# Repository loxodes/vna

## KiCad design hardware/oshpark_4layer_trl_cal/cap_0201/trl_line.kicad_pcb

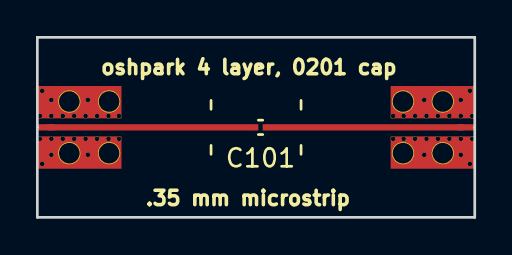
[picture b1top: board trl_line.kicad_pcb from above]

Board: 4 copper layers, 24.3 x 10.0 mm, 3 parts (0 on the bottom side), 3 nets.

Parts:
C101: C_Small; C_0201
U101, U102: CONN_SMA_2GND; SMA_901-10512_6p7MIL_FR408_CPW_LAUNCH

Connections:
GND: U101.2, U101.3, U102.2, U102.3
unnamed: C101.1, U102.1
unnamed: C101.2, U101.1

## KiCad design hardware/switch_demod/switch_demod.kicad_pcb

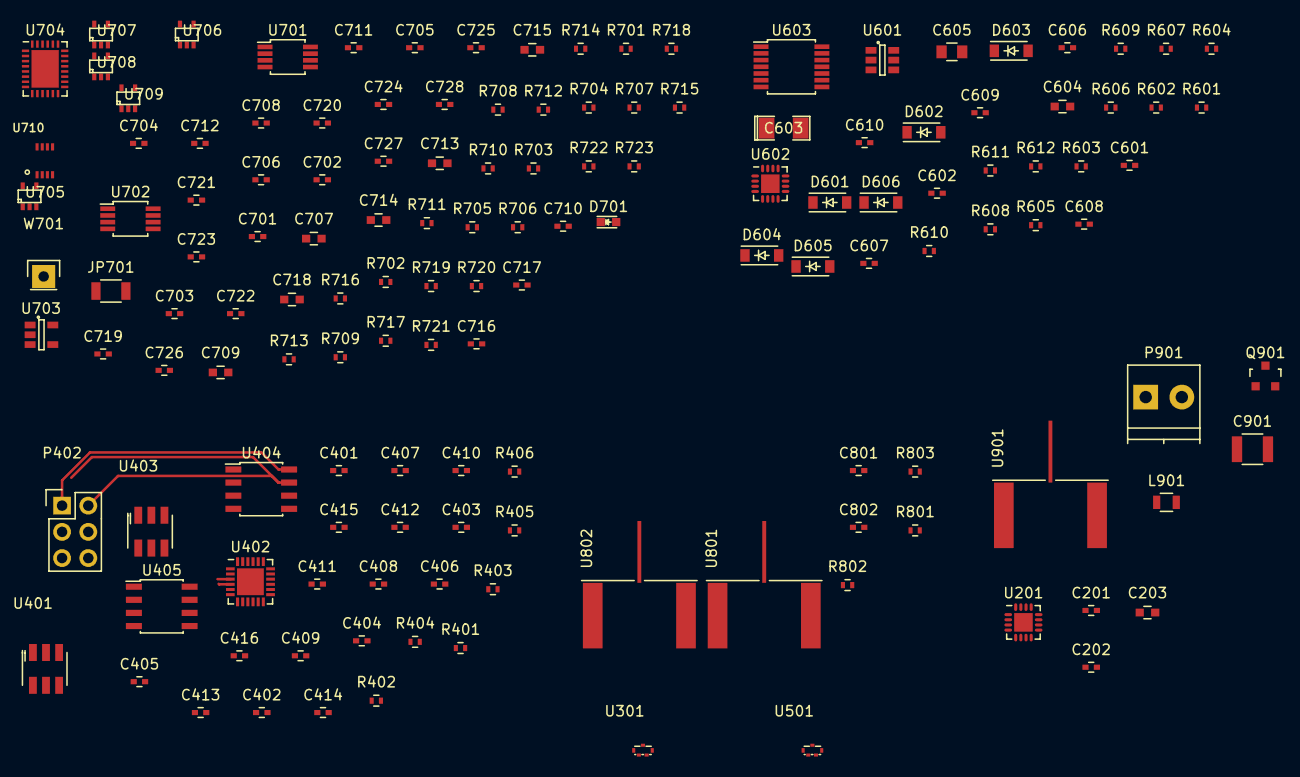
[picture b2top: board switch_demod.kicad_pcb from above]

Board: 4 copper layers, 141 parts (0 on the bottom side), 98 nets.

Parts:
C201, C202, C401, C404, C405, C406, C407, C408, C409, C410, C412, C606, C609: 100 pF; C_0402
C203, C604, C707, C709, C713, C714, C718: 10 uF; C_0603
C402, C403, C411, C413, C414, C415, C416, C602, C607, C701, C702, C705, C706, C708, C711, C712, C719, C720, C721, C722, C723, C724, C725, C726, C727, C728: 100 nF; C_0402
C601, C608: 30 pF; C_0402
C603: 10 uF TANT; SMD-1206_Pol
C605: C_Small; C_0805
C610, C801, C802: C_Small; C_0402
C703, C704: 220 pF; C_0402
C710, C716, C717: 1 uF; C_0402
C715: 10 nF; C_0603
C901: 100 uF; C_1210
D601, D602, D603, D604, D605, D606: 3.3V; SOD-123
D701: LED; LED_0603
JP701: JUMPER; R_1206
L901: FERRITE CHIP; R_0805
P402: CONN_02X03; Pin_Header_Straight_2x03
P901: CONN_01X02; TerminalBlock_Pheonix_PT-3.5mm_2pol
Q901: DMG2305UX; SOT-23
R401, R403, R404, R405, R406, R601, R602, R603, R610, R611, R612: 10k; R_0402
R402: 470; R_0402
R604, R605, R606, R607, R608, R609: 100; R_0402
R701, R702, R704, R706, R716: 0; R_0402
R703, R717, R718, R801, R802, R803: 1k; R_0402
R705, R707, R713: DNP; R_0402
R708, R709, R710, R711, R714, R715: 25; R_0402
R712, R719, R720, R721, R722, R723: 10; R_0402
U201: PE42521; QFN-16-1EP_3x3mm_Pitch0.5mm
U301, U501: PWR_SPLITTER; PS1608
U401, U403: TCM-63AX+; TCM1-63AX+
U402: ADL5380; QFN-24-1EP_4x4mm_Pitch0.5mm
U404, U405: LTC1566-1; SOIC-8_3.9x4.9mm_Pitch1.27mm
U601: LTC1983; SOT-23-6
U602: HMC424; QFN-16-1EP_3x3mm_Pitch0.5mm
U603: 74HC04_FULL; TSSOP-14_4.4x5mm_Pitch0.65mm
U701, U702: LT1819; MSOP-8_3x3mm_Pitch0.65mm
U703: TPS793; SOT-23-5
U704: LTC2323; QFN-28-1EP_4x5mm_Pitch0.5mm
U705, U706, U707, U708, U709: NC7SVU04; SC-70-5
U710: NC7SV74KBX; US8
U801, U802, U901: CONN_SMA_2GND; 142-0721-882_sma_cutout
W701: TEST_1P; Pin_Header_Straight_1x01

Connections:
+2V5: C718.1, C719.1, C720.1, C722.2, C728.2, D701.2, JP701.2, R716.2, R723.1, U703.5, U704.14, U706.5, U710.7, U710.8
+5V: C202.1, C203.1, C402.2, C403.2, C404.2, C405.2, C410.2, C411.2, C415.2, C416.2, C601.2, C602.2, C603.1, C701.2, C702.2, C705.1, C706.1, C707.1, C708.1, C709.1, C710.2, C727.1, C901.1, L901.1, R402.1, R405.1, R406.1, U201.16, U402.6, U402.13, U402.24, U404.6, U405.6, U601.1, U601.6, U701.8, U702.8, U703.1, U703.3, U704.1, U704.8, U704.28
/adc/ADC_CLKOUT: R719.2, U704.17, U705.4
/adc/ADC_CONV_CLK_IN: C721.2, R714.2
/adc/ADC_CONV_CLK_OUT: U707.4, U710.1
/adc/ADC_I_N: P402.6, R707.2, U405.7, U702.5
/adc/ADC_I_P: P402.5, U405.8, U702.3
/adc/ADC_Q_N: P402.2, R705.2, U404.7, U701.5
/adc/ADC_Q_P: P402.1, U404.8, U701.3
/adc/ADC_SCK: R722.2, U704.21, U706.4
/adc/ADC_SDO1: R720.2, U704.15, U708.4
/adc/ADC_SDO2: R721.2, U704.19, U709.4
/adc/ADC_~CONV: U704.9, U710.3
/adc/AIN1+: C704.1, R710.1, U704.7
/adc/AIN1-: C704.2, R711.1, U704.6
/adc/AIN2+: C703.1, R708.1, U704.2
/adc/AIN2-: C703.2, R709.1, U704.3
/attenuator/ATT_IN: C606.2, U501.3
/attenuator/ATT_OUT: C609.1, U301.3
/attenuator/V1: R604.2, U602.9
/attenuator/V2: R605.2, U602.8
/attenuator/V3: R606.2, U602.7
/attenuator/V4: R609.1, U602.6
/attenuator/V5: R608.1, U602.5
/attenuator/V6: R607.1, U602.4
/connectors_control_pow/DEMOD_ENBL: R401.1, U402.7
/demod/DEMOD_LO: C412.2, U501.2
/demod/DEMOD_RF: C401.2, U201.7
/demod/I_ADL_N: U402.4, U405.2
/demod/I_ADL_P: U402.3, U405.1
/demod/LO_I_N: C408.1, U402.10
/demod/LO_I_P: C409.1, U402.9
/demod/LO_Q_N: C407.1, U402.21
/demod/LO_Q_P: C406.1, U402.22
/demod/Q_ADL_N: U402.15, U404.2
/demod/Q_ADL_P: U402.16, U404.1
/panel connectors/DUT_PORT1: C801.2, U301.1
/panel connectors/DUT_PORT2: C802.2, U201.11
/splitter_input/RF2: C201.1, U301.2
/splitter_lo/RFC: U501.1, U901.1
GND: C202.2, C203.2, C402.1, C403.1, C404.1, C405.1, C410.1, C411.1, C413.2, C414.2, C415.1, C416.1, C601.1, C602.1, C603.2, C604.2, C607.1, C608.1, C610.1, C701.1, C702.1, C705.2, C706.2, C707.2, C708.2, C709.2, C710.1, C715.2, C716.2, C717.2, C718.2, C719.2, C720.2, C722.1, C723.1, C724.1, C725.1, C726.1, C727.2, C728.1, C901.2, P402.3, P402.4, P901.2, Q901.1, R401.2, R403.2, R404.2, R703.1, R705.1, R707.1, R712.1, R713.2, R715.1, R718.1, R801.1, R802.1, R803.1, U201.1, U201.3, U201.4, U201.5, U201.6, U201.8, U201.9, U201.10, U201.12, U201.13, U201.15, U201.17, U301.4, U401.3, U402.1, U402.2, U402.5, U402.8, U402.11, U402.14, U402.17, U402.18, U402.20, U402.23, U402.25, U403.3, U404.4, U405.4, U501.4, U601.5, U602.1, U602.3, U602.10, U602.12, U602.17, U603.14, U701.4, U702.4, U703.2, U704.4, U704.5, U704.10, U704.23, U704.29, U705.3, U706.3, U707.3, U708.3, U709.3, U710.4, U801.2, U801.3, U802.2, U802.3, U901.2, U901.3, W701.1
unnamed: C201.2, U201.2
unnamed: C401.1, U401.2
unnamed: C406.2, U401.6
unnamed: C407.2, U401.4
unnamed: C408.2, U403.6
unnamed: C409.2, U403.4
unnamed: C412.1, U403.2
unnamed: C413.1, R403.1, R405.2, U404.3, U404.5
unnamed: C414.1, R404.1, R406.2, U405.3, U405.5
unnamed: C605.1, U601.4
unnamed: C605.2, U601.3
unnamed: C606.1, U602.2
unnamed: C609.2, U602.11
unnamed: C711.1, C713.1, U704.26
unnamed: C711.2, C713.2, U704.27
unnamed: C712.1, C714.1, U704.12
unnamed: C712.2, C714.2, U704.11
unnamed: C715.1, U703.4
unnamed: C716.1, U704.24
unnamed: C717.1, U704.13
unnamed: C721.1, R717.1, R718.2, U707.2
unnamed: C724.2, R716.1, R717.2, U707.5
unnamed: C801.1, U801.1
unnamed: C802.1, U802.1
unnamed: D601.2, R601.1, U603.1
unnamed: D602.2, R602.1, U603.3
unnamed: D603.2, R603.1, U603.5
unnamed: D604.2, R612.1, U603.13
unnamed: D605.2, R611.1, U603.11
unnamed: D606.2, R610.1, U603.9
unnamed: D701.1, R703.2
unnamed: L901.2, Q901.2
unnamed: R402.2, U402.19
unnamed: R604.1, U603.2
unnamed: R605.1, U603.4
unnamed: R606.1, U603.6
unnamed: R607.2, U603.12
unnamed: R608.2, U603.10
unnamed: R609.2, U603.8
unnamed: R701.1, U701.2
unnamed: R701.2, R708.2, U701.1
unnamed: R702.1, U702.2
unnamed: R702.2, R710.2, U702.1
unnamed: R704.1, R709.2, U701.7
unnamed: R704.2, U701.6
unnamed: R706.1, R711.2, U702.7
unnamed: R706.2, U702.6
unnamed: R712.2, U704.25
unnamed: R713.1, U704.18
unnamed: R714.1, R715.2
unnamed: R719.1, U705.2
unnamed: R720.1, U708.2
unnamed: R721.1, U709.2
unnamed: R722.1, U706.2
unnamed: R723.2, U710.2
VEE: C604.1, C607.2, C608.2, C610.2, R601.2, R602.2, R603.2, R610.2, R611.2, R612.2, U601.2, U602.15, U603.7
VMEM: C723.2, C725.2, C726.2, JP701.1, U705.5, U708.5, U709.5

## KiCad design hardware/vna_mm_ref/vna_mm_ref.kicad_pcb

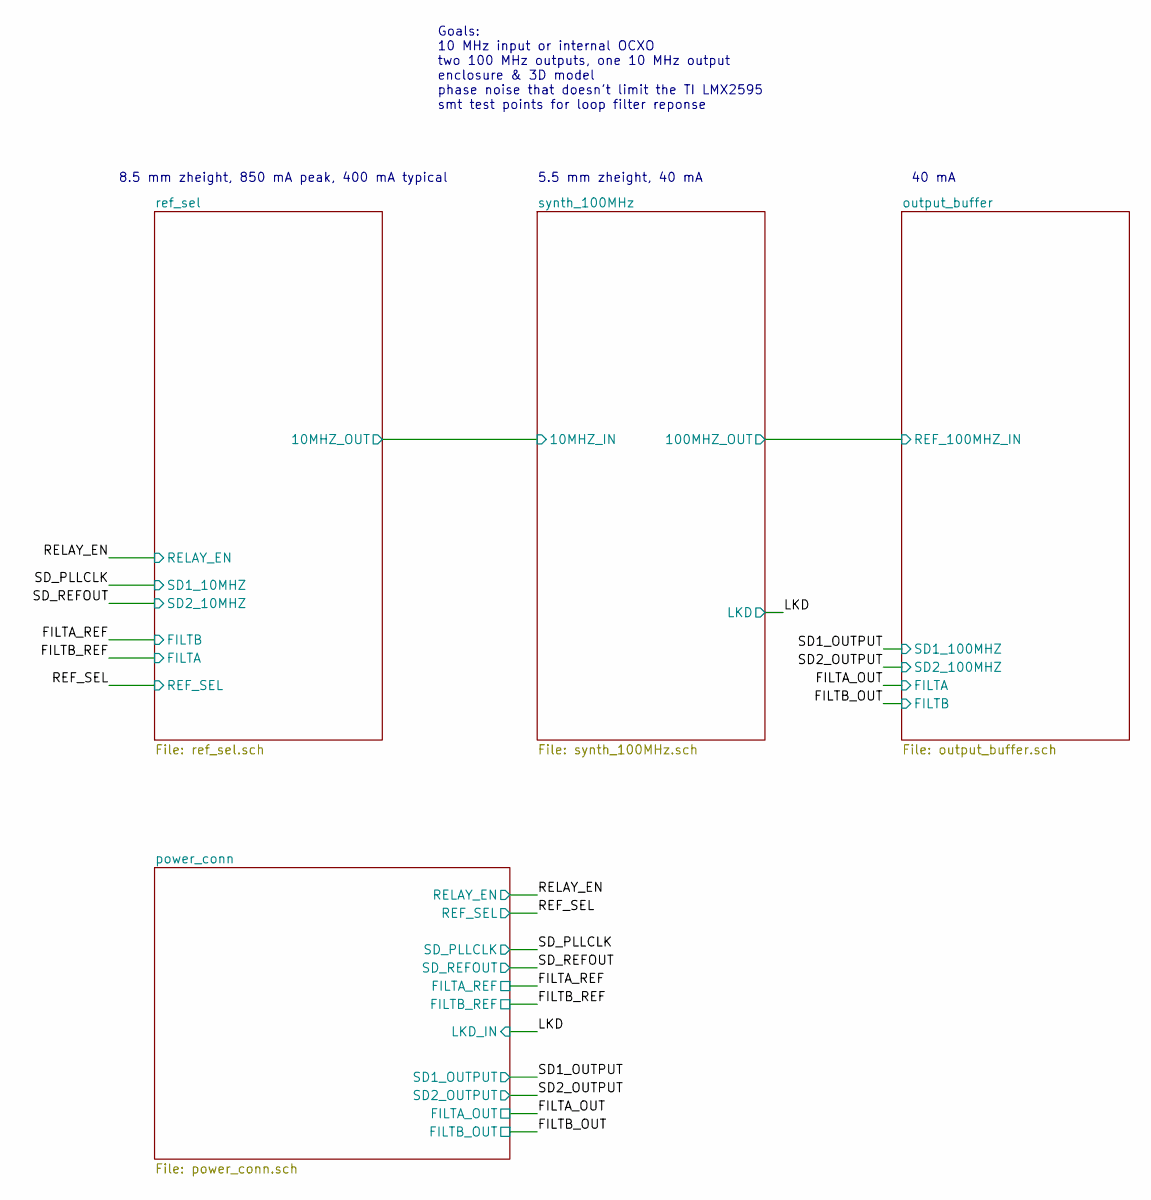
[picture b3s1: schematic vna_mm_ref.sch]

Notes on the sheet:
Goals: 10 MHz input or internal OCXO two 100 MHz outputs, one 10 MHz output enclosure & 3D model phase noise that doesn't limit the TI LMX2595 smt test points for loop filter reponse
8.5 mm zheight, 850 mA peak, 400 mA typical
5.5 mm zheight, 40 mA
40 mA

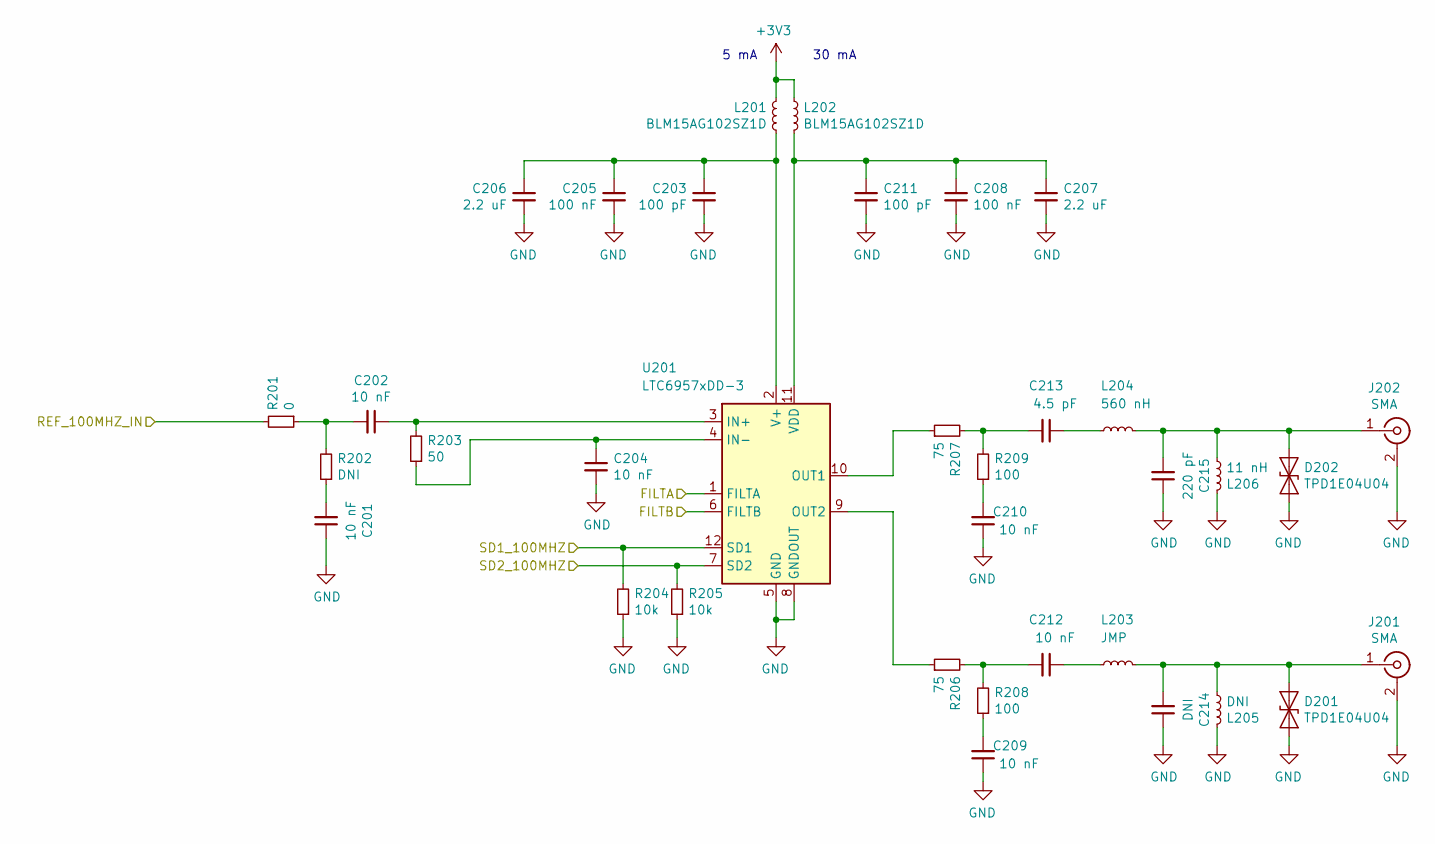
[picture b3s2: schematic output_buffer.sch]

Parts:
C201, C202, C204, C209, C210, C212: 10 nF; C_0402_1005Metric
C203, C211: 100 pF; C_0402_1005Metric
C205, C208: 100 nF; C_0402_1005Metric
C206, C207: 2.2 uF; C_0603_1608Metric
C213: 4.5 pF; C_0402_1005Metric
C214: DNI; C_0402_1005Metric
C215: 220 pF; C_0402_1005Metric
D201, D202: TPD1E04U04; D_0402_1005Metric
J201, J202: SMA; SMA_Amphenol_132289_EdgeMount
L201, L202: BLM15AG102SZ1D; L_0402_1005Metric
L203: JMP; L_0805_2012Metric
L204: 560 nH; L_0805_2012Metric
L205: DNI; L_0402_1005Metric
L206: 11 nH; L_0402_1005Metric
R201: 0; R_0402_1005Metric
R202: DNI; R_0402_1005Metric
R203: 50; R_0402_1005Metric
R204, R205: 10k; R_0402_1005Metric
R206, R207: 75; R_0402_1005Metric
R208, R209: 100; R_0402_1005Metric
U201: LTC6957xDD-3; DFN-12-1EP_3x3mm_P0.45mm_EP1.66x2.38mm

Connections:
+3V3: L201.1, L202.1; also elsewhere on the board
/FILTA_OUT: U201.1 (FILTA); also elsewhere on the board
/FILTB_OUT: U201.6 (FILTB); also elsewhere on the board
/SD1_OUTPUT: R204.2, U201.12 (SD1); also elsewhere on the board
/SD2_OUTPUT: R205.2, U201.7 (SD2); also elsewhere on the board
/synth_100MHz/100MHZ_OUT: R201.2; also elsewhere on the board
GND: C201.1, C203.2, C204.2, C205.2, C206.2, C207.2, C208.2, C209.1, C210.1, C211.2, C214.1, C215.1, D201.2 (A2), D202.2 (A2), J201.2 (Ext), J202.2 (Ext), L205.1, L206.1, R204.1, R205.1, U201.5 (GND), U201.8 (GNDOUT), U201.13 (GND); also elsewhere on the board
unnamed: C201.2, R202.1
unnamed: C202.1, R203.2, U201.3 (IN+)
unnamed: C202.2, R201.1, R202.2
unnamed: C203.1, C205.1, C206.1, L201.2, U201.2 (V+)
unnamed: C204.1, R203.1, U201.4 (IN-)
unnamed: C207.1, C208.1, C211.1, L202.2, U201.11 (VDD)
unnamed: C209.2, R208.1
unnamed: C210.2, R209.1
unnamed: C212.1, L203.2
unnamed: C212.2, R206.2, R208.2
unnamed: C213.1, L204.2
unnamed: C213.2, R207.2, R209.2
unnamed: C214.2, D201.1 (A1), J201.1 (In), L203.1, L205.2
unnamed: C215.2, D202.1 (A1), J202.1 (In), L204.1, L206.2
unnamed: R206.1, U201.9 (OUT2)
unnamed: R207.1, U201.10 (OUT1)

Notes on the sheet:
5 mA
30 mA

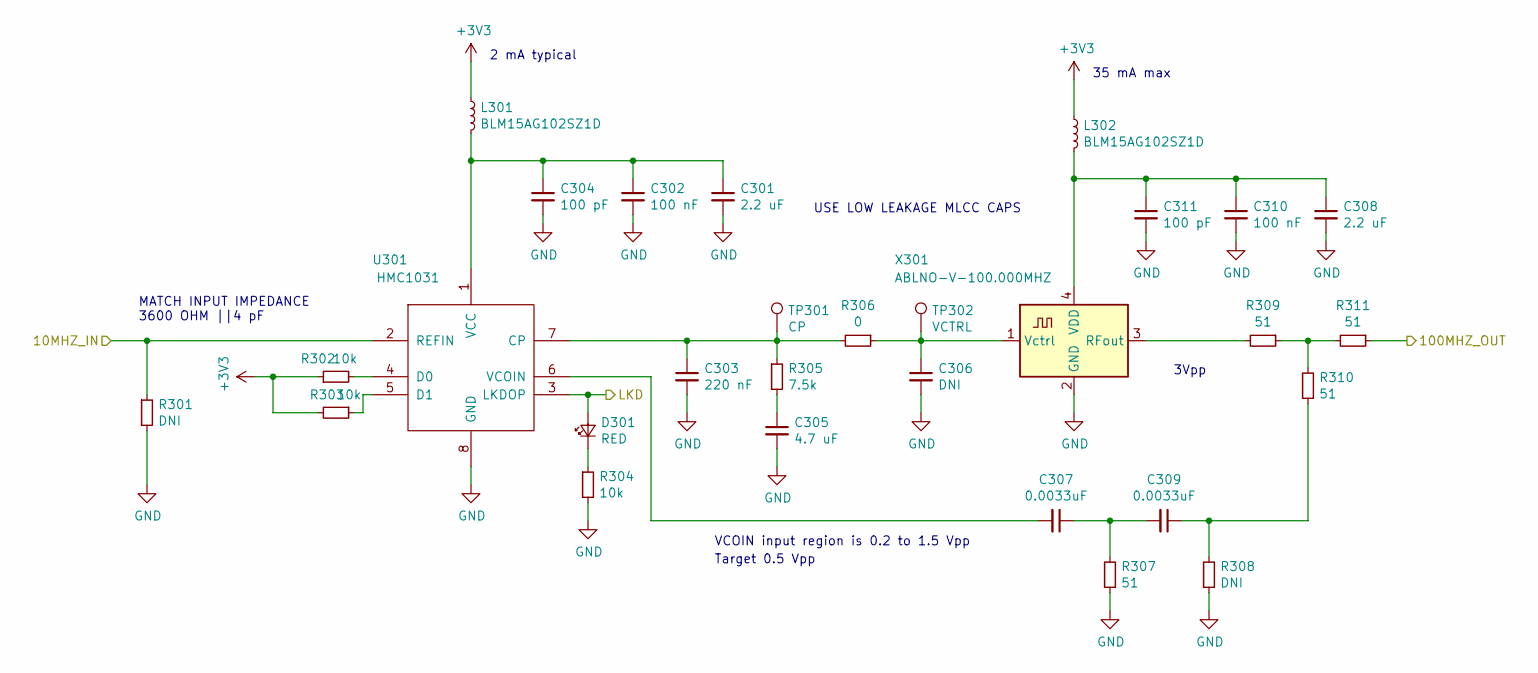
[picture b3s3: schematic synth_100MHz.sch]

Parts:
C301, C308: 2.2 uF; C_0603_1608Metric
C302, C310: 100 nF; C_0402_1005Metric
C303: 220 nF; C_0402_1005Metric
C304, C311: 100 pF; C_0402_1005Metric
C305: 4.7 uF; C_0603_1608Metric
C306: DNI; C_0402_1005Metric
C307, C309: 0.0033uF; C_0402_1005Metric
D301: RED; LED_0603_1608Metric
L301, L302: BLM15AG102SZ1D; L_0402_1005Metric
R301, R308: DNI; R_0402_1005Metric
R302, R303, R304: 10k; R_0402_1005Metric
R305: 7.5k; R_0402_1005Metric
R306: 0; R_0402_1005Metric
R307, R309, R310, R311: 51; R_0402_1005Metric
TP301: CP; TestPoint_Keystone_5015_Micro-Minature
TP302: VCTRL; TestPoint_Keystone_5015_Micro-Minature
U301: HMC1031; MSOP-8_3x3mm_P0.65mm
X301: ABLNO-V-100.000MHZ; Oscillator_SMD_Abracon_ABLNO

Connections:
+3V3: L301.1, L302.1, R302.1, R303.2; also elsewhere on the board
/LKD: D301.2 (A), U301.3 (LKDOP); also elsewhere on the board
/synth_100MHz/10MHZ_IN: R301.1, U301.2 (REFIN); also elsewhere on the board
/synth_100MHz/100MHZ_OUT: R311.1; also elsewhere on the board
GND: C301.2, C302.2, C303.2, C304.2, C305.2, C306.2, C308.2, C310.2, C311.2, R301.2, R304.2, R307.1, R308.1, U301.8 (GND), X301.2 (GND); also elsewhere on the board
unnamed: C301.1, C302.1, C304.1, L301.2, U301.1 (VCC)
unnamed: C303.1, R305.1, R306.2, TP301.1, U301.7 (CP)
unnamed: C305.1, R305.2
unnamed: C306.1, R306.1, TP302.1, X301.1 (Vctrl)
unnamed: C307.1, C309.2, R307.2
unnamed: C307.2, U301.6 (VCOIN)
unnamed: C308.1, C310.1, C311.1, L302.2, X301.4 (VDD)
unnamed: C309.1, R308.2, R310.1
unnamed: D301.1 (K), R304.1
unnamed: R302.2, U301.4 (D0)
unnamed: R303.1, U301.5 (D1)
unnamed: R309.1, R310.2, R311.2
unnamed: R309.2, X301.3 (RFout)

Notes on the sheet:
USE LOW LEAKAGE MLCC CAPS
2 mA typical
35 mA max
MATCH INPUT IMPEDANCE 3600 OHM ||4 pF
VCOIN input region is 0.2 to 1.5 Vpp
3Vpp
Target 0.5 Vpp

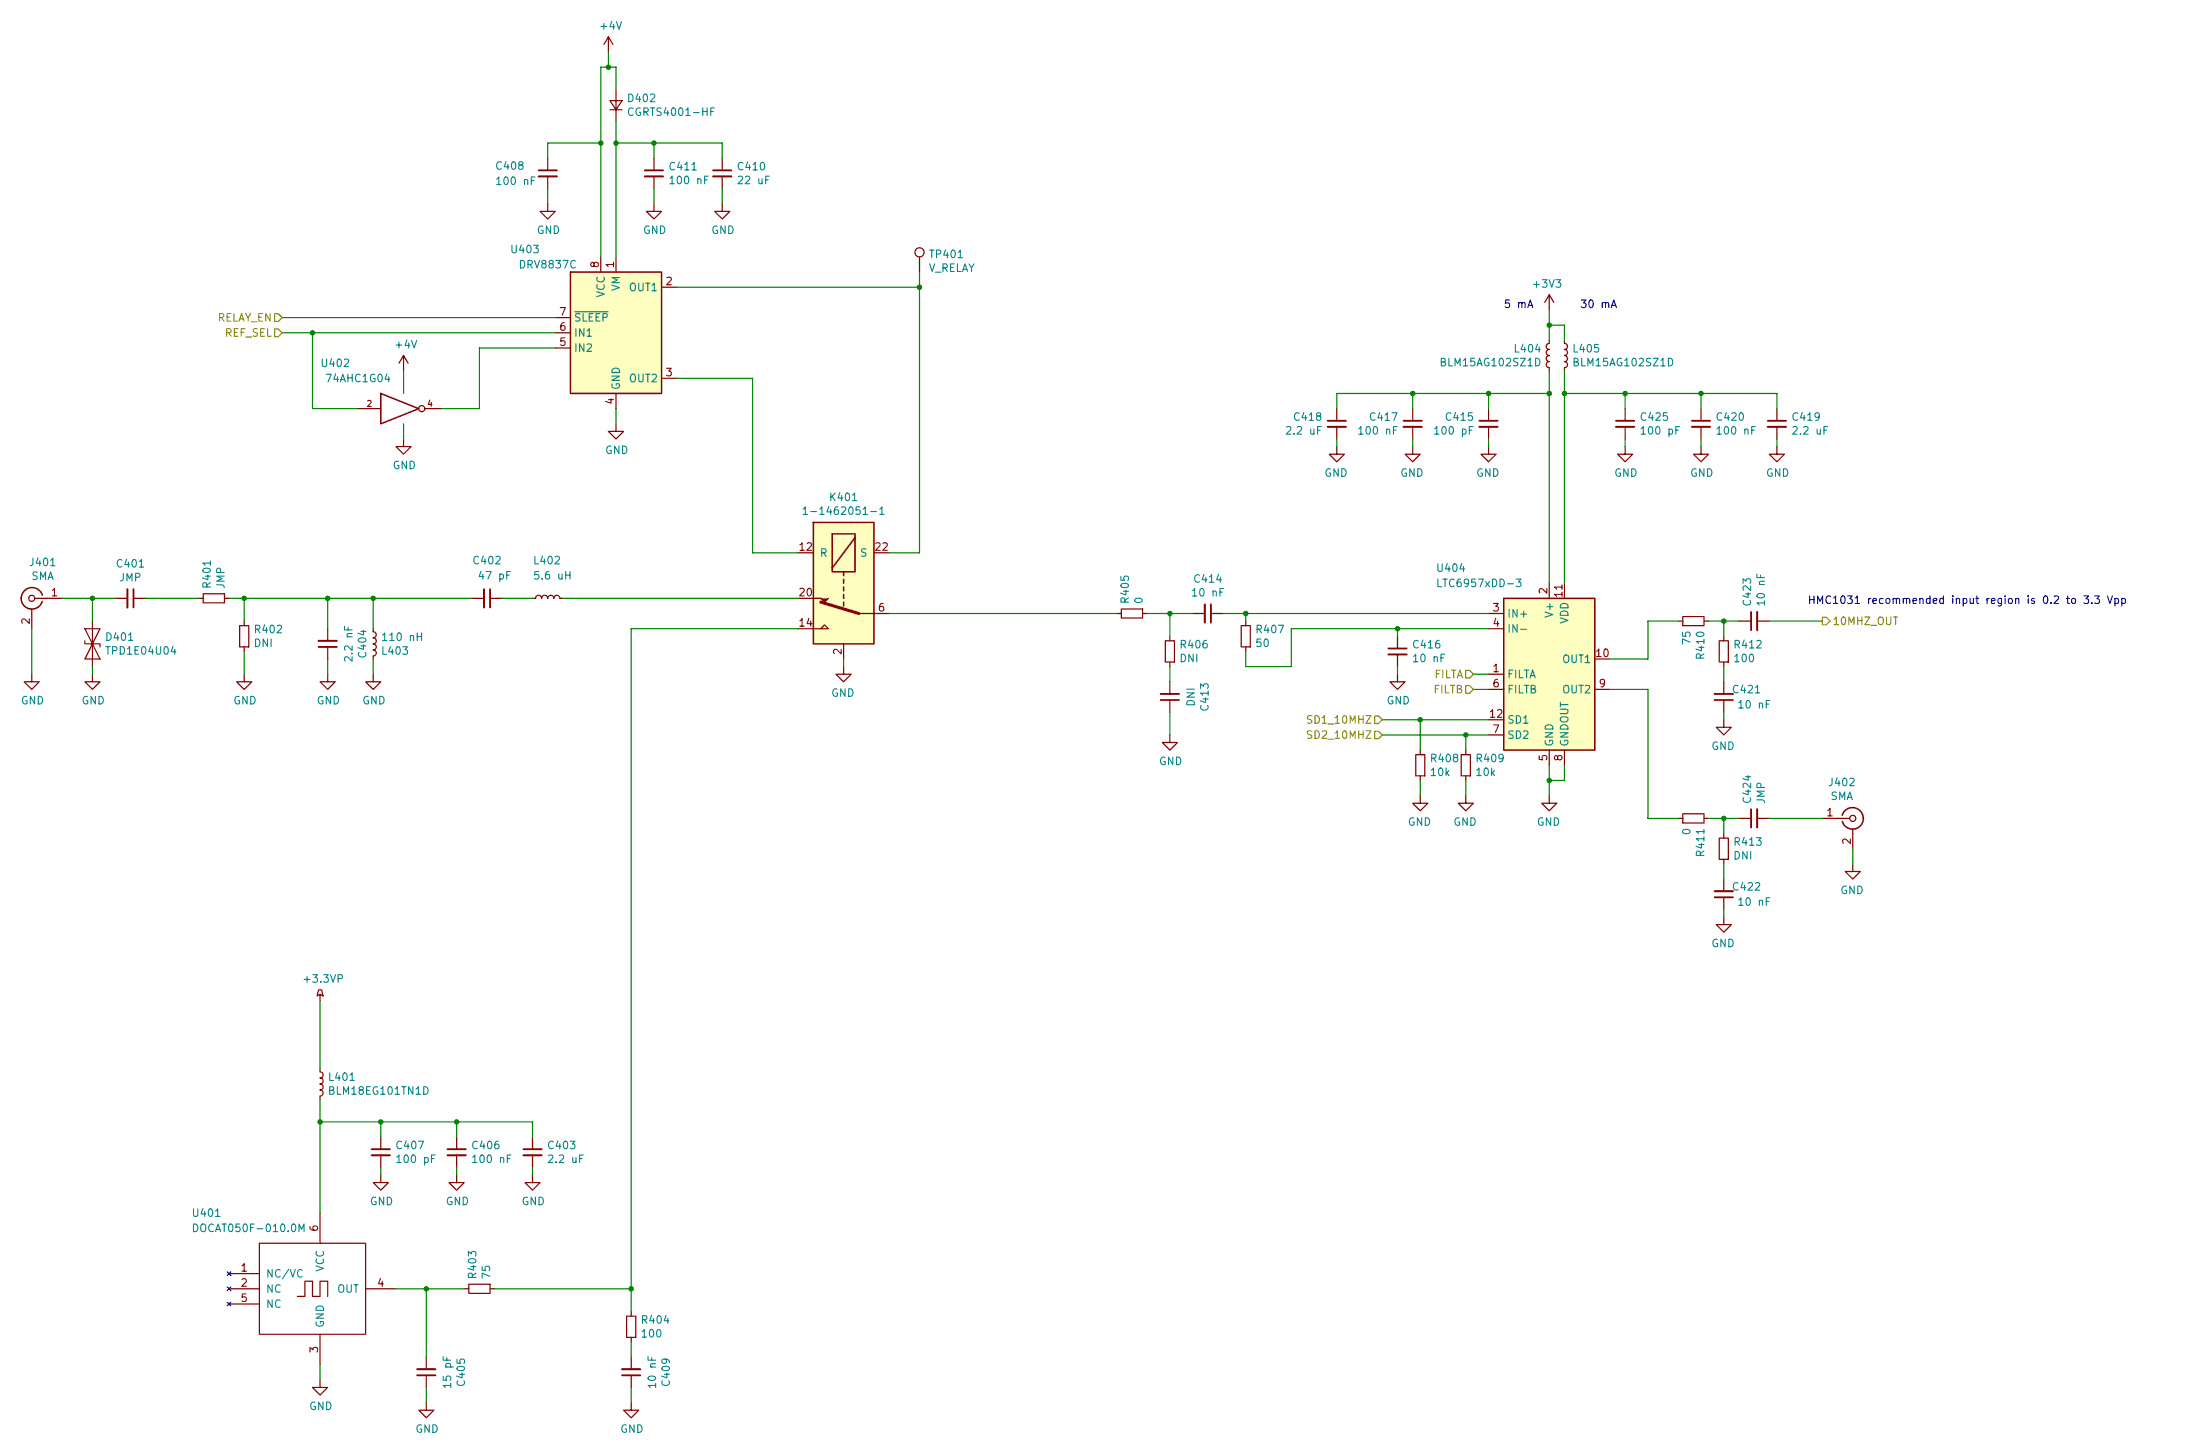
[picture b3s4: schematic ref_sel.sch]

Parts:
C401, C424: JMP; C_0402_1005Metric
C402: 47 pF; C_0402_1005Metric
C403, C418, C419: 2.2 uF; C_0603_1608Metric
C404: 2.2 nF; C_0402_1005Metric
C405: 15 pF; C_0402_1005Metric
C406, C408, C411, C417, C420: 100 nF; C_0402_1005Metric
C407, C415, C425: 100 pF; C_0402_1005Metric
C409, C414, C416, C421, C422, C423: 10 nF; C_0402_1005Metric
C410: 22 uF; C_0805_2012Metric
C413: DNI; C_0402_1005Metric
D401: TPD1E04U04; D_0402_1005Metric
D402: CGRTS4001-HF; D_SOD-123F
J401, J402: SMA; SMA_Amphenol_132289_EdgeMount
K401: 1-1462051-1; Relay_SPDT_AXICOM_HF3Series_50ohms_Pitch1.27mm
L401: BLM18EG101TN1D; L_0603_1608Metric
L402: 5.6 uH; L_0805_2012Metric
L403: 110 nH; L_0603_1608Metric
L404, L405: BLM15AG102SZ1D; L_0402_1005Metric
R401: JMP; R_0402_1005Metric
R402, R406, R413: DNI; R_0402_1005Metric
R403, R410: 75; R_0402_1005Metric
R404, R412: 100; R_0402_1005Metric
R405, R411: 0; R_0402_1005Metric
R407: 50; R_0402_1005Metric
R408, R409: 10k; R_0402_1005Metric
TP401: V_RELAY; TestPoint_Keystone_5015_Micro-Minature
U401: DOCAT050F-010.0M; DOCAT_9.1x14.1mm
U402: 74AHC1G04; SOT-353_SC-70-5
U403: DRV8837C; WSON-8-1EP_2x2mm_P0.5mm_EP0.9x1.6mm
U404: LTC6957xDD-3; DFN-12-1EP_3x3mm_P0.45mm_EP1.66x2.38mm

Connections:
+3.3VP: L401.1; also elsewhere on the board
+3V3: L404.1, L405.1; also elsewhere on the board
+4V: C408.1, D402.2 (A), U402.5 (VCC), U403.8 (VCC); also elsewhere on the board
/FILTA_REF: U404.6 (FILTB); also elsewhere on the board
/FILTB_REF: U404.1 (FILTA); also elsewhere on the board
/REF_SEL: U402.2, U403.6 (IN1); also elsewhere on the board
/RELAY_EN: U403.7 (~SLEEP); also elsewhere on the board
/SD_PLLCLK: R408.2, U404.12 (SD1); also elsewhere on the board
/SD_REFOUT: R409.2, U404.7 (SD2); also elsewhere on the board
/synth_100MHz/10MHZ_IN: C423.2; also elsewhere on the board
GND: C403.2, C404.1, C405.1, C406.2, C407.2, C408.2, C409.1, C410.2, C411.2, C413.1, C415.2, C416.2, C417.2, C418.2, C419.2, C420.2, C421.1, C422.1, C425.2, D401.2 (A2), J401.2 (Ext), J402.2 (Ext), K401.2, K401.5, K401.7, K401.10, K401.13, K401.15, K401.17, K401.19, K401.21, L403.1, R402.1, R408.1, R409.1, U401.3 (GND), U402.3 (GND), U403.4 (GND), U403.9 (GND), U404.5 (GND), U404.8 (GNDOUT), U404.13 (GND); also elsewhere on the board
unnamed: C401.1, R401.2
unnamed: C401.2, D401.1 (A1), J401.1 (In)
unnamed: C402.1, L402.2
unnamed: C402.2, C404.2, L403.2, R401.1, R402.2
unnamed: C403.1, C406.1, C407.1, L401.2, U401.6 (VCC)
unnamed: C405.2, R403.2, U401.4 (OUT)
unnamed: C409.2, R404.1
unnamed: C410.1, C411.1, D402.1 (K), U403.1 (VM)
unnamed: C413.2, R406.1
unnamed: C414.1, R407.2, U404.3 (IN+)
unnamed: C414.2, R405.1, R406.2
unnamed: C415.1, C417.1, C418.1, L404.2, U404.2 (V+)
unnamed: C416.1, R407.1, U404.4 (IN-)
unnamed: C419.1, C420.1, C425.1, L405.2, U404.11 (VDD)
unnamed: C421.2, R412.1
unnamed: C422.2, R413.1
unnamed: C423.1, R410.2, R412.2
unnamed: C424.1, R411.2, R413.2
unnamed: C424.2, J402.1 (In)
unnamed: K401.1, K401.12 (R), U403.3 (OUT2)
unnamed: K401.6, R405.2
unnamed: K401.11, K401.22 (S), TP401.1, U403.2 (OUT1)
unnamed: K401.14, R403.1, R404.2
unnamed: K401.20, L402.1
unnamed: R410.1, U404.10 (OUT1)
unnamed: R411.1, U404.9 (OUT2)
unnamed: U402.4, U403.5 (IN2)

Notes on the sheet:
5 mA
30 mA
HMC1031 recommended input region is 0.2 to 3.3 Vpp

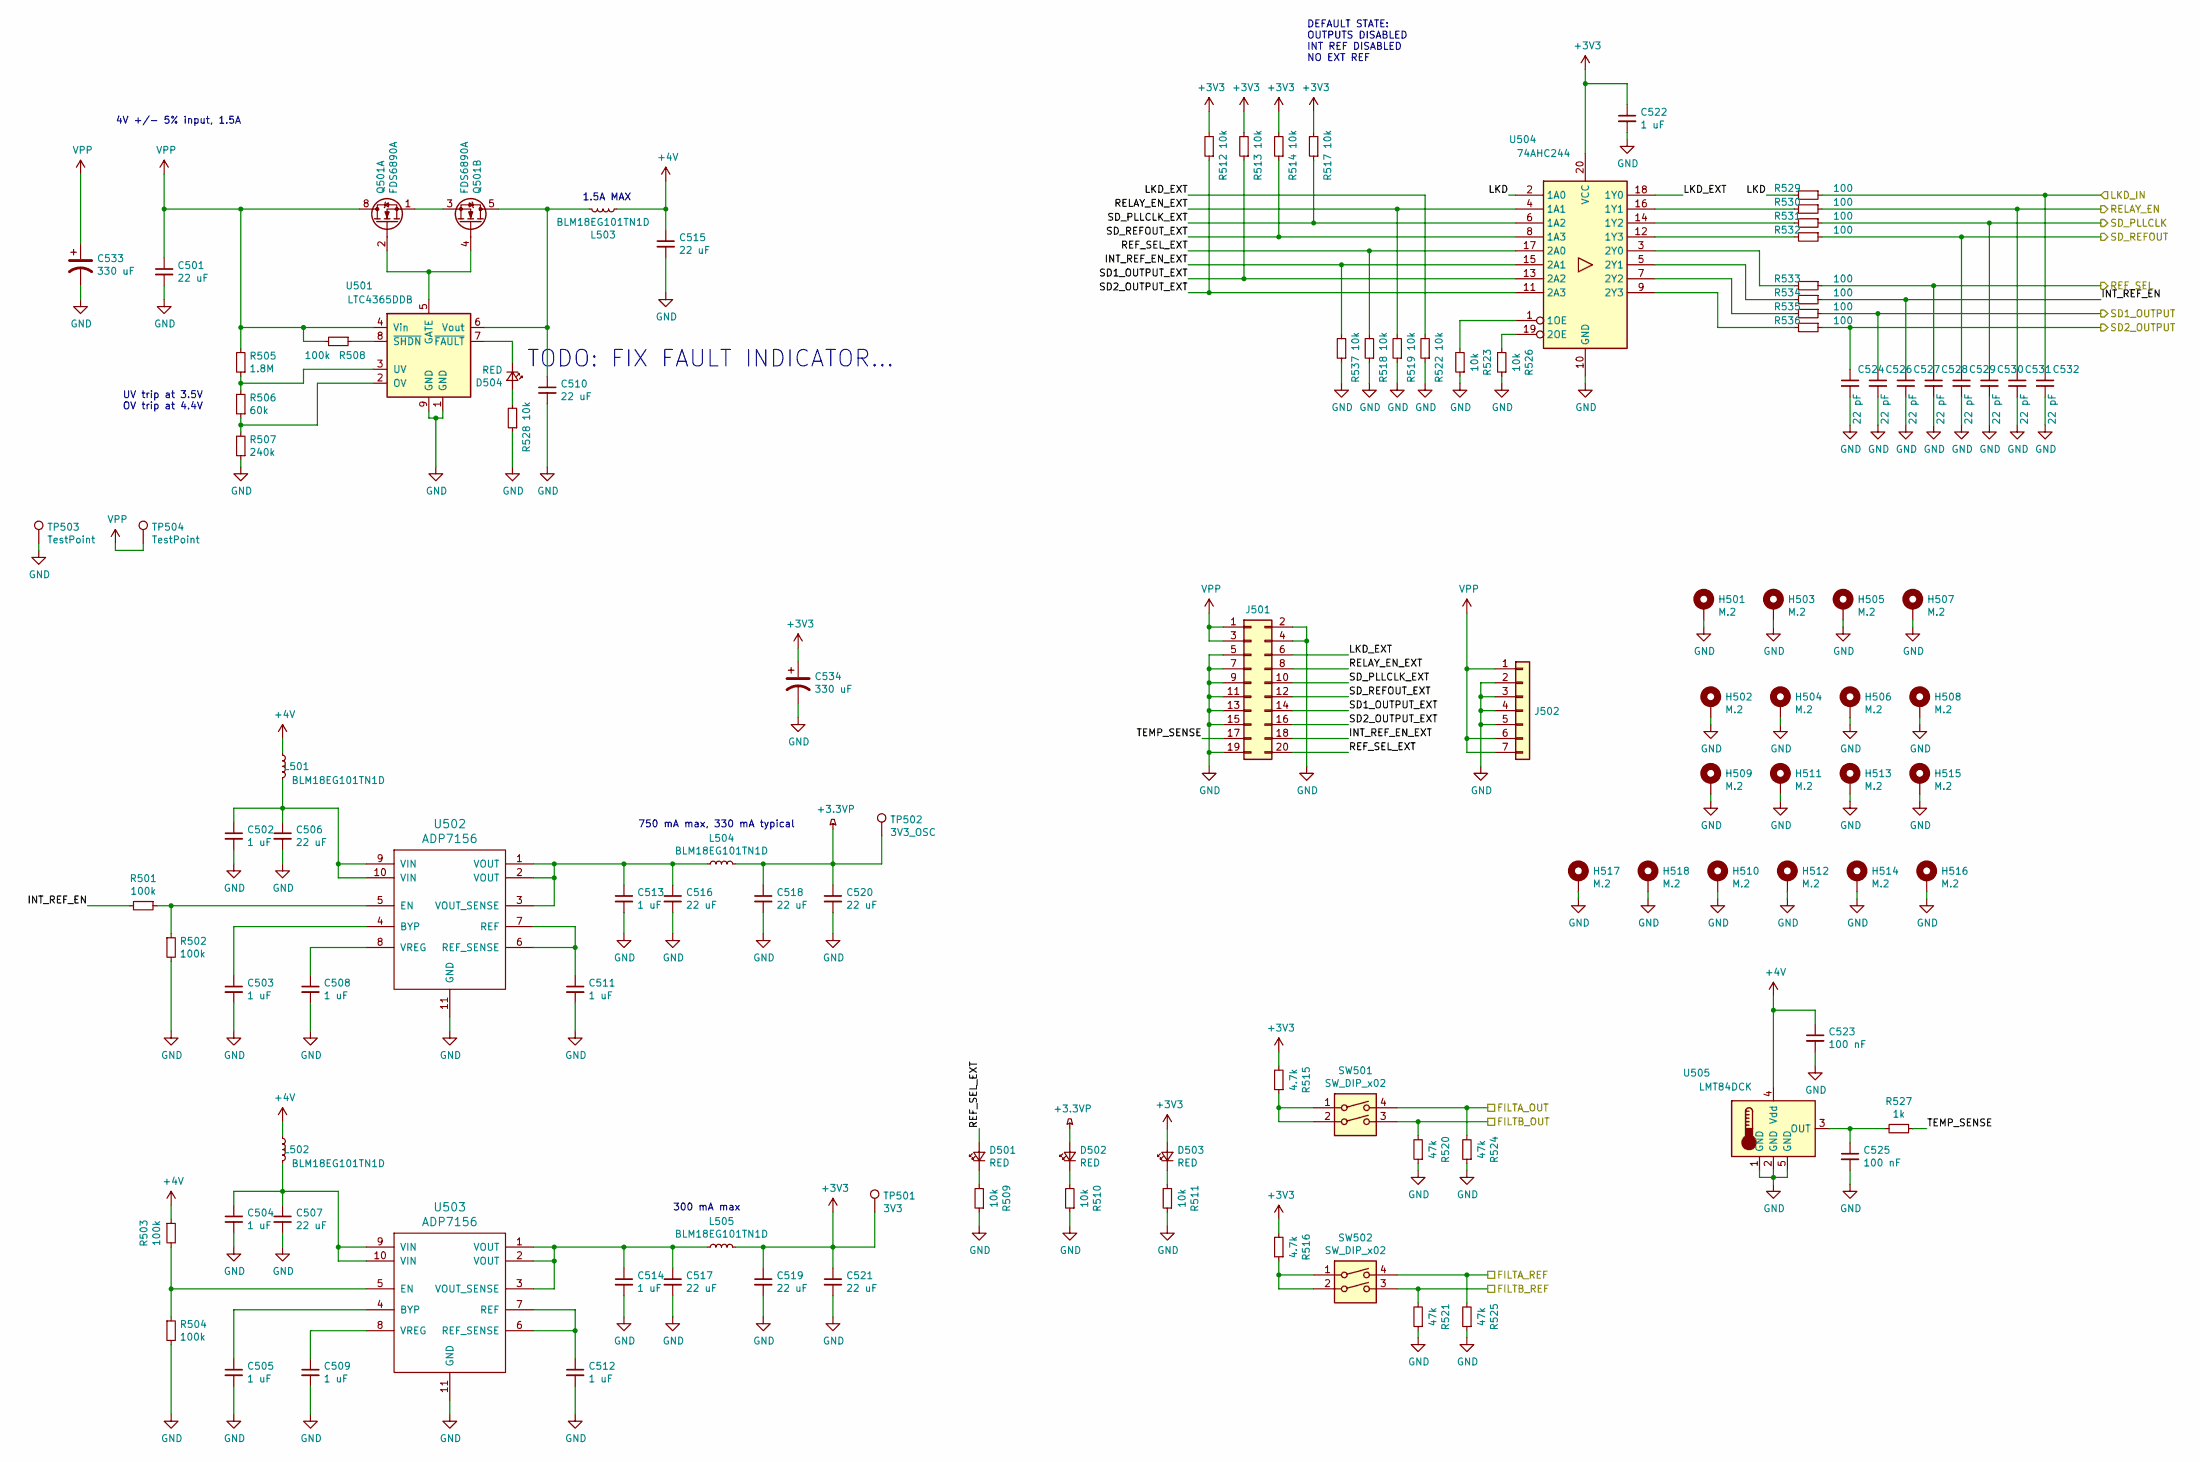
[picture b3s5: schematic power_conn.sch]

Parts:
C501, C506, C507, C510, C515, C516, C517, C518, C519, C520, C521: 22 uF; C_0805_2012Metric
C502, C503, C504, C505, C508, C509, C511, C512, C513, C514, C522: 1 uF; C_0402_1005Metric
C523, C525: 100 nF; C_0402_1005Metric
C524, C526, C527, C528, C529, C530, C531, C532: 22 pF; C_0402_1005Metric
C533, C534: 330 uF; CP_Elec_6.3x5.9
D501, D502, D503, D504: RED; LED_0603_1608Metric
H501, H502, H503, H504, H505, H506, H507, H508, H509, H510, H511, H512, H513, H514, H515, H516, H517, H518: M.2; MountingHole_2.2mm_M2_Pad_Via
J501: Conn_02x10_Odd_Even; PinHeader_2x10_P2.54mm_Vertical
J502: Conn_01x07; PinHeader_1x07_P2.54mm_Vertical
L501, L502, L503, L504, L505: BLM18EG101TN1D; L_0603_1608Metric
Q501: FDS6890A; SOIC-8_3.9x4.9mm_P1.27mm
R501, R502, R503, R504, R508: 100k; R_0402_1005Metric
R505: 1.8M; R_0402_1005Metric
R506: 60k; R_0402_1005Metric
R507: 240k; R_0402_1005Metric
R509, R510, R511, R512, R513, R514, R517, R518, R519, R522, R523, R526, R528, R537: 10k; R_0402_1005Metric
R515, R516: 4.7k; R_0402_1005Metric
R520, R521, R524, R525: 47k; R_0402_1005Metric
R527: 1k; R_0402_1005Metric
R529, R530, R531, R532, R533, R534, R535, R536: 100; R_0402_1005Metric
SW501, SW502: SW_DIP_x02; SW_DIP_SPSTx02_Slide_6.7x6.64mm_W6.73mm_P2.54mm_LowProfile_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
TP501: 3V3; TestPoint_Keystone_5015_Micro-Minature
TP502: 3V3_OSC; TestPoint_Keystone_5015_Micro-Minature
TP503, TP504: TestPoint; TURRET_MILLMAX_2101
U501: LTC4365DDB; DFN-8-1EP_2x3mm_P0.5mm_EP0.61x2.2mm
U502, U503: ADP7156; DFN-10-1EP_3x3mm_P0.5mm_EP1.65x2.38mm
U504: 74AHC244; TSSOP-20_4.4x6.5mm_P0.65mm
U505: LMT84DCK; SOT-353_SC-70-5

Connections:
+3.3VP: C518.1, C520.1, D502.2 (A), L504.2, TP502.1; also elsewhere on the board
+3V3: C519.1, C521.1, C522.1, C534.1, D503.2 (A), L505.2, R512.2, R513.2, R514.2, R515.2, R516.2, R517.2, TP501.1, U504.20 (VCC); also elsewhere on the board
+4V: C515.1, C523.1, L501.1, L502.1, L503.1, R503.1, U505.4 (Vdd); also elsewhere on the board
/FILTA_OUT: R524.2, SW501.4; also elsewhere on the board
/FILTA_REF: R525.2, SW502.4; also elsewhere on the board
/FILTB_OUT: R520.2, SW501.3; also elsewhere on the board
/FILTB_REF: R521.2, SW502.3; also elsewhere on the board
/LKD: C532.1, R529.1; also elsewhere on the board
/REF_SEL: C528.1, R533.1; also elsewhere on the board
/RELAY_EN: C531.1, R530.1; also elsewhere on the board
/SD1_OUTPUT: C526.1, R535.1; also elsewhere on the board
/SD2_OUTPUT: C524.1, R536.1; also elsewhere on the board
/SD_PLLCLK: C530.1, R531.1; also elsewhere on the board
/SD_REFOUT: C529.1, R532.1; also elsewhere on the board
/power_conn/INT_REF_EN: C527.1, R501.2, R534.1
/power_conn/INT_REF_EN_EXT: J501.18, R537.2, U504.15 (2A1)
/power_conn/LKD: R529.2, U504.2 (1A0)
/power_conn/LKD_EXT: J501.6, R522.2, U504.18 (1Y0)
/power_conn/REF_SEL_EXT: D501.2 (A), J501.20, R518.2, U504.17 (2A0)
/power_conn/RELAY_EN_EXT: J501.8, R519.2, U504.4 (1A1)
/power_conn/SD1_OUTPUT_EXT: J501.14, R513.1, U504.13 (2A2)
/power_conn/SD2_OUTPUT_EXT: J501.16, R512.1, U504.11 (2A3)
/power_conn/SD_PLLCLK_EXT: J501.10, R517.1, U504.6 (1A2)
/power_conn/SD_REFOUT_EXT: J501.12, R514.1, U504.8 (1A3)
/power_conn/TEMP_SENSE: J501.17, R527.1
GND: C501.2, C502.2, C503.2, C504.2, C505.2, C506.2, C507.2, C508.2, C509.2, C510.2, C511.2, C512.2, C513.2, C514.2, C515.2, C516.2, C517.2, C518.2, C519.2, C520.2, C521.2, C522.2, C523.2, C524.2, C525.2, C526.2, C527.2, C528.2, C529.2, C530.2, C531.2, C532.2, C533.2, C534.2, H501.1, H502.1, H503.1, H504.1, H505.1, H506.1, H507.1, H508.1, H509.1, H510.1, H511.1, H512.1, H513.1, H514.1, H515.1, H516.1, H517.1, H518.1, J501.2, J501.4, J501.5, J501.7, J501.9, J501.11, J501.13, J501.15, J501.19, J502.2, J502.3, J502.4, J502.5, R502.2, R504.2, R507.1, R509.1, R510.1, R511.1, R518.1, R519.1, R520.1, R521.1, R522.1, R523.1, R524.1, R525.1, R526.1, R528.1, R537.1, TP503.1, U501.1 (GND), U501.9 (GND), U502.11 (GND), U503.11 (GND), U504.10 (GND), U505.1 (GND), U505.2 (GND), U505.5 (GND); also elsewhere on the board
unnamed: C502.1, C506.1, L501.2, U502.9 (VIN), U502.10 (VIN)
unnamed: C503.1, U502.4 (BYP)
unnamed: C504.1, C507.1, L502.2, U503.9 (VIN), U503.10 (VIN)
unnamed: C505.1, U503.4 (BYP)
unnamed: C508.1, U502.8 (VREG)
unnamed: C509.1, U503.8 (VREG)
unnamed: C510.1, L503.2, Q501.5 (D2), Q501.6 (D2), U501.6 (Vout)
unnamed: C511.1, U502.6 (REF_SENSE), U502.7 (REF)
unnamed: C512.1, U503.6 (REF_SENSE), U503.7 (REF)
unnamed: C513.1, C516.1, L504.1, U502.1 (VOUT), U502.2 (VOUT), U502.3 (VOUT_SENSE)
unnamed: C514.1, C517.1, L505.1, U503.1 (VOUT), U503.2 (VOUT), U503.3 (VOUT_SENSE)
unnamed: C525.1, R527.2, U505.3 (OUT)
unnamed: D501.1 (K), R509.2
unnamed: D502.1 (K), R510.2
unnamed: D503.1 (K), R511.2
unnamed: D504.1 (K), U501.7 (~FAULT)
unnamed: D504.2 (A), R528.2
unnamed: Q501.1 (S1), Q501.3 (S2)
unnamed: Q501.2 (G1), Q501.4 (G2), U501.5 (GATE)
unnamed: R501.1, R502.1, U502.5 (EN)
unnamed: R503.2, R504.1, U503.5 (EN)
unnamed: R505.1, R506.2, U501.3 (UV)
unnamed: R506.1, R507.2, U501.2 (OV)
unnamed: R508.1, U501.8 (~SHDN)
unnamed: R515.1, SW501.1, SW501.2
unnamed: R516.1, SW502.1, SW502.2
unnamed: R523.2, U504.1 (1OE)
unnamed: R526.2, U504.19 (2OE)
unnamed: R530.2, U504.16 (1Y1)
unnamed: R531.2, U504.14 (1Y2)
unnamed: R532.2, U504.12 (1Y3)
unnamed: R533.2, U504.3 (2Y0)
unnamed: R534.2, U504.5 (2Y1)
unnamed: R535.2, U504.7 (2Y2)
unnamed: R536.2, U504.9 (2Y3)
VPP: C501.1, C533.1, J501.1, J501.3, J502.1, J502.6, J502.7, Q501.7 (D1), Q501.8 (D1), R505.2, R508.2, TP504.1, U501.4 (Vin)

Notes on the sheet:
300 mA max
1.5A MAX
750 mA max, 330 mA typical
4V +/- 5% input, 1.5A
UV trip at 3.5V OV trip at 4.4V
DEFAULT STATE: OUTPUTS DISABLED INT REF DISABLED NO EXT REF
TODO: FIX FAULT INDICATOR...

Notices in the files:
parts and their libraries:
Copyright 2016 Accelerated Designs. All rights reserved.
